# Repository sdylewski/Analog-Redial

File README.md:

**Home** · [1 · Get a board](docs/board.md) · [2 · Parts & assembly](docs/bom.md) · [3 · Flash & test](docs/flashing.md) · [4 · Set up & use](docs/setup.md)

<h1 align="center">Analog Redial</h1>

<p align="center">
  <b>Bring old telephones back to life.</b><br>
  Plug in one or two analog phones, rotary or touch-tone, and they get real
  dial tone, ringing, an operator recording and an answering machine: a complete standalone phone system.<br>
  Hackable open source hardware and software with a working web UI for configuration.</p>

<p align="center">
  <a href="#everything-it-connects-to">Overview</a> ·
  <a href="#what-can-i-do-with-it">What it does</a> ·
  <a href="#set-it-up-from-your-browser">Web interface</a> ·
  <a href="#what-does-one-cost">Cost</a> ·
  <a href="#build-one">Build one</a> ·
  <a href="#community">Community</a>
</p>

<table>
  <tr>
    <td width="50%"></td>
    <td width="50%"></td>
  </tr>
  <tr>
    <td align="center">The board: an ESP32-C6, an audio codec, with dual phone lines and the bluetooth module.</td>
    <td align="center">In its 3D-printed case <br>(<a href="https://github.com/sdylewski/Analog-Redial/blob/main/docs/case.md">case guide and print files</a>)</td>
  </tr>
</table>

## What can I do with it?

| | What you get | What you need |
|---|---|---|
| **Offline Calling** | Two phones, one board. Dial **321** (configurable) and the other phone rings.  No Wi-Fi required. Use in 2 rooms of a house or a fun toy for kids| 2 phones |
| **A phone that does things** | Dial a code and something happens: play a clip, leave a message, hear a joke. For museum exhibits, art pieces, a wedding guestbook phone. Add your own codes and audio from the browser. | One phone |
| **Call between boards** | Put a board in each room. Each gets its own 4-digit number the first time it's on your Wi-Fi; dial another board's number and its phone rings. It's VoIP over your home network: no server needed. | Two or more boards <br> Wi-Fi |
| **VoIP server** | Register a line with Asterisk, FreePBX or any SIP server and call anything that server can reach, at home or away. If the server goes down, the boards can still call each other directly. | One phone <br> Wi-Fi <br> SIP server |
| **Home Assistant** | Every pickup, hang-up and dial code becomes an event, so a dial code can turn on a light and the phone can ring when your doorbell does. Over MQTT or a plain webhook. *Experimental.* | Wi-Fi and Home Assistant (or any MQTT broker) |
| **Switch things** | Dial a code and a pin goes high for a few seconds or continuously: a relay, a buzzer, a lamp. | One line <br> no microSD <br> a relay |
| **Bluetooth calls** | Pair your mobile and the rotary phone becomes its handset: the bell rings for incoming calls, lift to answer, dial out on the rotary dial. | The BM64 Bluetooth board |

### Why not just buy a VoIP adapter?

You can do a lot with VoIP adapters and an Asterisk server, but this system can work fully offline if desired while also adding VoIP when needed.  There's also the possibility of uSD card access, bluetooth, or 4 GPIO pins to do even more.

## System overview

Every network option runs on the board's own Wi-Fi, with nothing to add.
Bluetooth is the only one that needs an extra board.

### The finer print

- **Dialing.** Rotary pulse and touch-tone, on either line. Dial codes can be
  up to 10 digits (spaces, dashes and parentheses are ignored). Add your own
  codes and audio clips from the browser and give any built-in
  code a different number. 
  	- Play an audio file after dialing a number: **412** plays dial-up modem sounds
  	- Respond to any number: **314** reads pi aloud.
  	- A kitchen timer: dial **846**, then the number of minutes, and the phone rings when time is up.
  	- An alarm clock: dial **256**, then the time (0730), and the phone rings at that time.
  	- A weather line: dial **1212** for the forecast, read out like the old time-and-temperature numbers.
  	- Optional digit readback speaks each digit you dial (**822**
  on, **821** off)
- **Calls.** Line-to-line calls with ringback and busy tones. 
	- Optional intercom mode: lift one handset, wait, and the other phone rings with its
  own double ring. 
  	- Optional VoIP calls (G.711): directly between Analog Redial boards on the same network, with no server, or through a SIP server such as Asterisk.
- **Sound.** Dial tone, ringback and busy that match your country (North
  America, several European countries, Japan, China, or a generic
  international set). Echo cancellation and earpiece volume per line. An
  off-hook alert if a handset is left off. Experimental voice effects
  (Dalek, chipmunk, robot) mid-call.
- **Messages.** Record a message with **211** and download it from the
  browser. 
  	- Optional per-line answering machine, each line with its own greeting,
  that also answers VoIP or local calls. 
  	- Storage to internal flash or microSD card for hours of storage
  (1-line version only). 
- **Payphones.** Dial tone, ringing, dialing and calls work on a payphone like
  on any phone; the coin mechanism isn't supported yet. See
  [Payphones](docs/setup.md#10-payphones).
- **Home automation.** Every pickup, hang-up, dial code and incoming ring
  can go to Home Assistant, or any system that takes a webhook or MQTT. Home
  Assistant can ring a phone or fire a pin output back. Experimental; see
  [Home Assistant](docs/home-assistant.md).
- **Things on the pins.** A dial code can switch one of four spare pins
  (a relay, a buzzer, a lamp) for a set number of seconds, or toggle it.
- **Day to day.** Quiet hours that silence the bell overnight. Remembers
  several Wi-Fi networks. An optional web password. Firmware updates from
  the browser. A one-button rescue mode for when it can't find its network.
  Board blink codes to indicate activity and errors.
- **Open.** ESP-IDF C firmware under the MIT license, KiCad hardware files,
  and a serial console for debugging.

Full feature list and firmware architecture: [Features](docs/features.md).

---

## Set it up from your browser

The board serves its own web page at **`http://phone.local`**, reachable
from any phone or laptop on your Wi-Fi. No app, no account, no cloud. On
first boot it makes its own Wi-Fi network with a setup page that gets it
onto yours. Firmware is updating frequently, so these are just examples.

<table>
  <tr>
    <td align="center" width="33%"><br><b>Status</b><br>Lines, activity, the dial guide</td>
    <td align="center" width="33%"><br><b>Phone settings</b><br>Answering machine, tones, effects</td>
    <td align="center" width="33%"><br><b>Dial codes</b><br>Your own codes and audio</td>
  </tr>
  <tr>
    <td align="center"><br><b>VoIP</b><br>SIP server, generated Asterisk script</td>
    <td align="center"><br><b>Recordings</b><br>Play or download messages</td>
    <td align="center"><br><b>Hardware</b><br>Line count, microSD, firmware update</td>
  </tr>
</table>

Click any picture for the full page. A guided tour is in
[Set up & use](docs/setup.md).

---

## What does one cost?

US prices from October 2026, including shipping and import tariff:

| | Per board | 5 boards |
|---|---:|---:|
| Assembled PCB from JLCPCB, delivered (5-board minimum) | $17.11 | $85.53 |
| Parts you solder, from DigiKey ([parts list](docs/bom.md)) | $19 | $95 |
| DigiKey shipping, about $5 an order | $1 | $5 |
| **Total, one phone line** | **about $37** | **about $186** |
| Second phone line (optional) | +$10 | +$50 |
| Bluetooth board (optional, v5) | +$15 | +$80 |

**Five boards cost about $186 in all, about $37 each.**
JLCPCB's minimum is five, so it's about $110 up front, with four spare PCBs.
The five-board Bluetooth figure is $15 a board plus about $5 shipping. Buying
the hand-solder parts from AliExpress saves $7 per board.

You'll also want a 2 A USB-C charger (or a regulated 5-6 V, 2 A DC supply for the DC jack; never 9 V or 12 V) and one or two analog phones. 

Most of a small order is fixed PCB setup fees, so boards get cheaper when people
order together. If you'd like a board,
**[fill out the interest form](https://forms.gle/kVKHiXejV6M2ZxC17)**. It's
only to show interest, so I can email you when boards are available on Tindie;
there's no commitment. Questions? [Join the Discord](https://discord.gg/zEZkqfcxqE) and ask there.

Price breakdown: [Get a board](docs/board.md#what-it-costs).

---
<br>

## Build one

No surface-mount soldering needed: the fab places the small parts, and
everything you solder is through-hole. If you can solder a header and type a
few commands in a terminal, you can build one.

| Step | Guide | What's in it |
|---|---|---|
| **1** | [Get a board](docs/board.md) | Board versions, ordering from JLCPCB, buying on Tindie, costs |
| **2** | [Parts](docs/bom.md) and [assembly](docs/building.md) | What to buy, soldering order, checks before power-on; [v5 step by step](docs/build-v5.md) |
| **3** | [Flash & test](docs/flashing.md) | Install ESP-IDF, flash the firmware, run the hardware self-test |
| **4** | [Set up & use](docs/setup.md) | Wi-Fi, the web interface, dial codes, your own audio |

Going further: [Troubleshooting](docs/troubleshooting.md) ·
[VoIP setup](docs/voip-setup.md) ·
[Home Assistant](docs/home-assistant.md) ·
[Board reference (v4)](docs/hardware-smd4.md) ·
[Board reference (v5)](docs/hardware-smd5.md) ·
[Features & firmware architecture](docs/features.md) ·
[Firmware developer notes](https://github.com/sdylewski/Analog-Redial/blob/main/firmware/README.md)

> ⚠️ **Phone lines carry real voltage.** The board drives about 48 V DC on
> an off-hook line and about 60 V AC while ringing, with peaks near 90 V.
> Don't touch the phone jacks or the line chips while it's powered, and never
> connect it to your house or telephone-company wiring. This is a hobby
> project, not certified telecom equipment.

---

## Community

- **Discord:** [join the server](https://discord.gg/zEZkqfcxqE) for questions, build help and show-and-tell
- **Want a board?** [Interest form](https://forms.gle/kVKHiXejV6M2ZxC17): just to show interest, so I can email you when boards are available on Tindie. Questions? Ask in the Discord.
- **Bugs and questions:** [GitHub Issues](https://github.com/sdylewski/Analog-Redial/issues)
- **Built one?** Post a picture in the Discord channel! We'd love to see it.

---

## Project history

| When | Version | What it was |
|------|---------|-------------|
| Aug 2020 | **Raspberry Pi** <br> | A Raspberry Pi 4 in a project box, two SLIC modules hand-wired on breadboard to the GPIO header, and a USB sound dongle per phone line. Hand written python software and shell scripts. No web UI, but it worked!|
| Jun 2026 | **v1** | The first ESP32 board: through-hole, with a WM8731 codec and two AG1170 SLICs. The Pi's job on a $5 microcontroller. Never built because boards got lost in the mail.|
| Jul 2026 | **v2** <br> | First surface-mount board: ESP32-C6 module, ES8388 codec, AG1171 SLICs, microSD. Required rework on audio lines and usb connection but it worked. |
| Sep 2026 | **v4** <br> | 2-layer, built around a cheaper 32-pin ESP32-C6-DevKitC-1, one or two phone lines, optional microSD. |
| Oct 2026 | **v5** <br>| Working: takes a genuine or clone ESP32-C6 module, and adds the expansion header (used for the Bluetooth board). <br>**With a clone module, remove the clone's bottom-right 5V pin** (see [Get a board](docs/board.md)). |
| Oct 2026 | **v5.1** | **RECOMMENDED VERSION** v5 with the clone-module 5V pin fixed (nothing to remove) and small silkscreen and fab-file updates. |
| Nov 2026 | **v6** <br> | **Released, not built or tested yet.** Two phone lines, the microSD card, payphone support and extra I/O all working at once (an I²C I/O expander drives the second line), plus the clone-module 5V pin fix and a 3 A diode (SS34) for the DC jack. |

### Related projects

Other open-source projects that bring old phones back to life:

| | [Analog Redial](https://github.com/sdylewski/Analog-Redial) | [RotaryCell](https://github.com/fregacmols/RotaryCell) | [weeBell](https://github.com/danjulio/weeBell_hardware) | [1dcoinctrl](https://github.com/hharte/1dcoinctrl) |
|---|---|---|---|---|
| **What it is** | Standalone phone system | Cellular conversion | Bluetooth adapter | Payphone coin controller |
| **MCU** | ESP32-C6 | ESP32 (LilyGO) | ESP32 (gCore) | PIC18F |
| **SLIC** | AG1171 | AG1171 | AG1171 | — |
| **Codec** | ES8388 | Passive | ES8388 | — |
| **Custom PCB** | ✅ | ✅ | ✅ | ✅ |
| **Rotary dial** | ✅ | ✅ | ✅ | ✅ |
| **Touch-tone (DTMF)** | ✅ | ❌ | ✅ | ❌ |
| **VoIP / SIP** | ✅ | ❌ | ❌ | ❌ |
| **Bluetooth calling** | ✅ | ❌ | ✅ | ❌ |
| **Cellular (SIM)** | ❌ | ✅ | ❌ | ❌ |
| **Web UI** | ✅ | ✅ Maintenance | ❌ LCD only | ❌ |
| **Answering machine** | ✅ | ❌ | ❌ | ❌ |
| **2nd phone line** | ✅ +$10 | ❌ | ❌ | ✅ Up to 4 |
| **Offline phone-to-phone** | ✅ | ❌ | ❌ | ❌ |
| **Dial codes & actions** | ✅ | ❌ | ❌ | ❌ |
| **Home automation** | ✅ | ❌ | ❌ | ❌ |
| **Payphone coin support** | In progress | ❌ | ❌ | ✅ +/-130 V |
| **OTA firmware update** | ✅ | ✅ | ❌ | ❌ |
| **Battery powered** | USB-C power bank | ✅ | ✅ | ❌ |
| **Approx. cost** | **~$37** (+$15 BT) | **~$60** + SIM | **~$60** shield + gCore (~$80-100) | **~$50-80** est. |
| **License** | MIT | MIT | CC0 | MIT |
| **GitHub stars** | — | 196 | 18 | 75 |

**RotaryCell** puts a cellular modem (LilyGO T-SIM7670G) and an AG1171
inside a rotary phone, turning it into a standalone battery-powered cell
phone with no Wi-Fi needed. It's the most polished project in the list,
with an illustrated build guide and multiple documented builds. The
published BOM is ~$52 for the core parts (LilyGO $29, PCBs $9, AG1171
$8.50, battery $5) plus a SIM card with ongoing service.

**weeBell** by [danjulio](https://github.com/danjulio) pairs a phone to
your cellphone via Bluetooth (the phone becomes a handset). It uses the
same ES8388 codec as Analog Redial, and the gCore it runs on brings a large
display. The POTS shield is
[available assembled on Tindie](https://www.tindie.com/products/30895/)
for about $60, but it also needs a [gCore](https://www.tindie.com/products/29204)
(ESP32 board with a 480 × 320 display, roughly $80-100) and an 18650
battery, so a complete build costs well over $140. weeBell replaces
danjulio's earlier Teensy-based Blue Pot.

**1dcoinctrl** by [hharte](https://github.com/hharte) is a coin-line
controller for Western Electric 1D/2D "dumb" payphones. It generates
+/-130 VDC for coin collect/refund and interfaces with Asterisk — the
closest existing project to the Analog Redial payphone coin board.
It requires a separate ATA and Asterisk server; it does not generate
dial tone or ring voltage itself. Cost is estimated at $50-80 for a
full 4-line build (PIC MCU, DC-DC converter, 7+ relays, PCB).

## License

[MIT](LICENSE) for the firmware and documentation. Hardware design files are
provided as-is for personal and hobby use; see the note in [`LICENSE`](LICENSE).

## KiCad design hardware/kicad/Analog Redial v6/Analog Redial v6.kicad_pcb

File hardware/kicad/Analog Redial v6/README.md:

# Analog Redial v6

**Released, not built or tested yet.** The KiCad project, a schematic PDF and the
JLCPCB fab files (`jlcpcb/`: gerbers, BOM and placement) are here, but no v6 board has
been built and its firmware support is untested. **v5** (`../Analog Redial v5/`) is
the tested board and **v5.1** (`../Analog Redial v5.1/`) is v5 with the
clone-module 5V pin fixed. Board reference: `docs/hardware-smd6.md`.

What v6 adds:

- **Everything at once:** two phone lines, the microSD card, payphone
  support and extra I/O all work together. On v4 and v5 the second line and
  the microSD card share the same four ESP32 pins, so a board has one or the
  other.
- **An I²C I/O expander** (TI TCA9534A, address 0x38) drives the second
  line's SLIC, which frees those ESP32 pins for the microSD card. Its four
  spare pins (P4-P7) come out on header J10 as extra I/O: the firmware drives
  them from pin dial codes (Settings → Dial Codes → Pin outputs), whatever the
  lines and microSD card are set to.
- **Payphone support:** a 5-pin I²C accessory header (1 GND, 2 SCL, 3 SDA,
  4 +3.3 V, 5 +5 V) for add-on boards such as the payphone coin board, itself
  sent to fab but untested (its firmware is in Settings → Payphone → Coin board).
- The clone-module footprint is corrected, so there is no pin to remove.
- A 3 A diode (SS34) between the DC jack and the +5 V rail instead of v5's
  1 A SS14.
- Larger vias on the power nets, teardrops, and updated silkscreen.

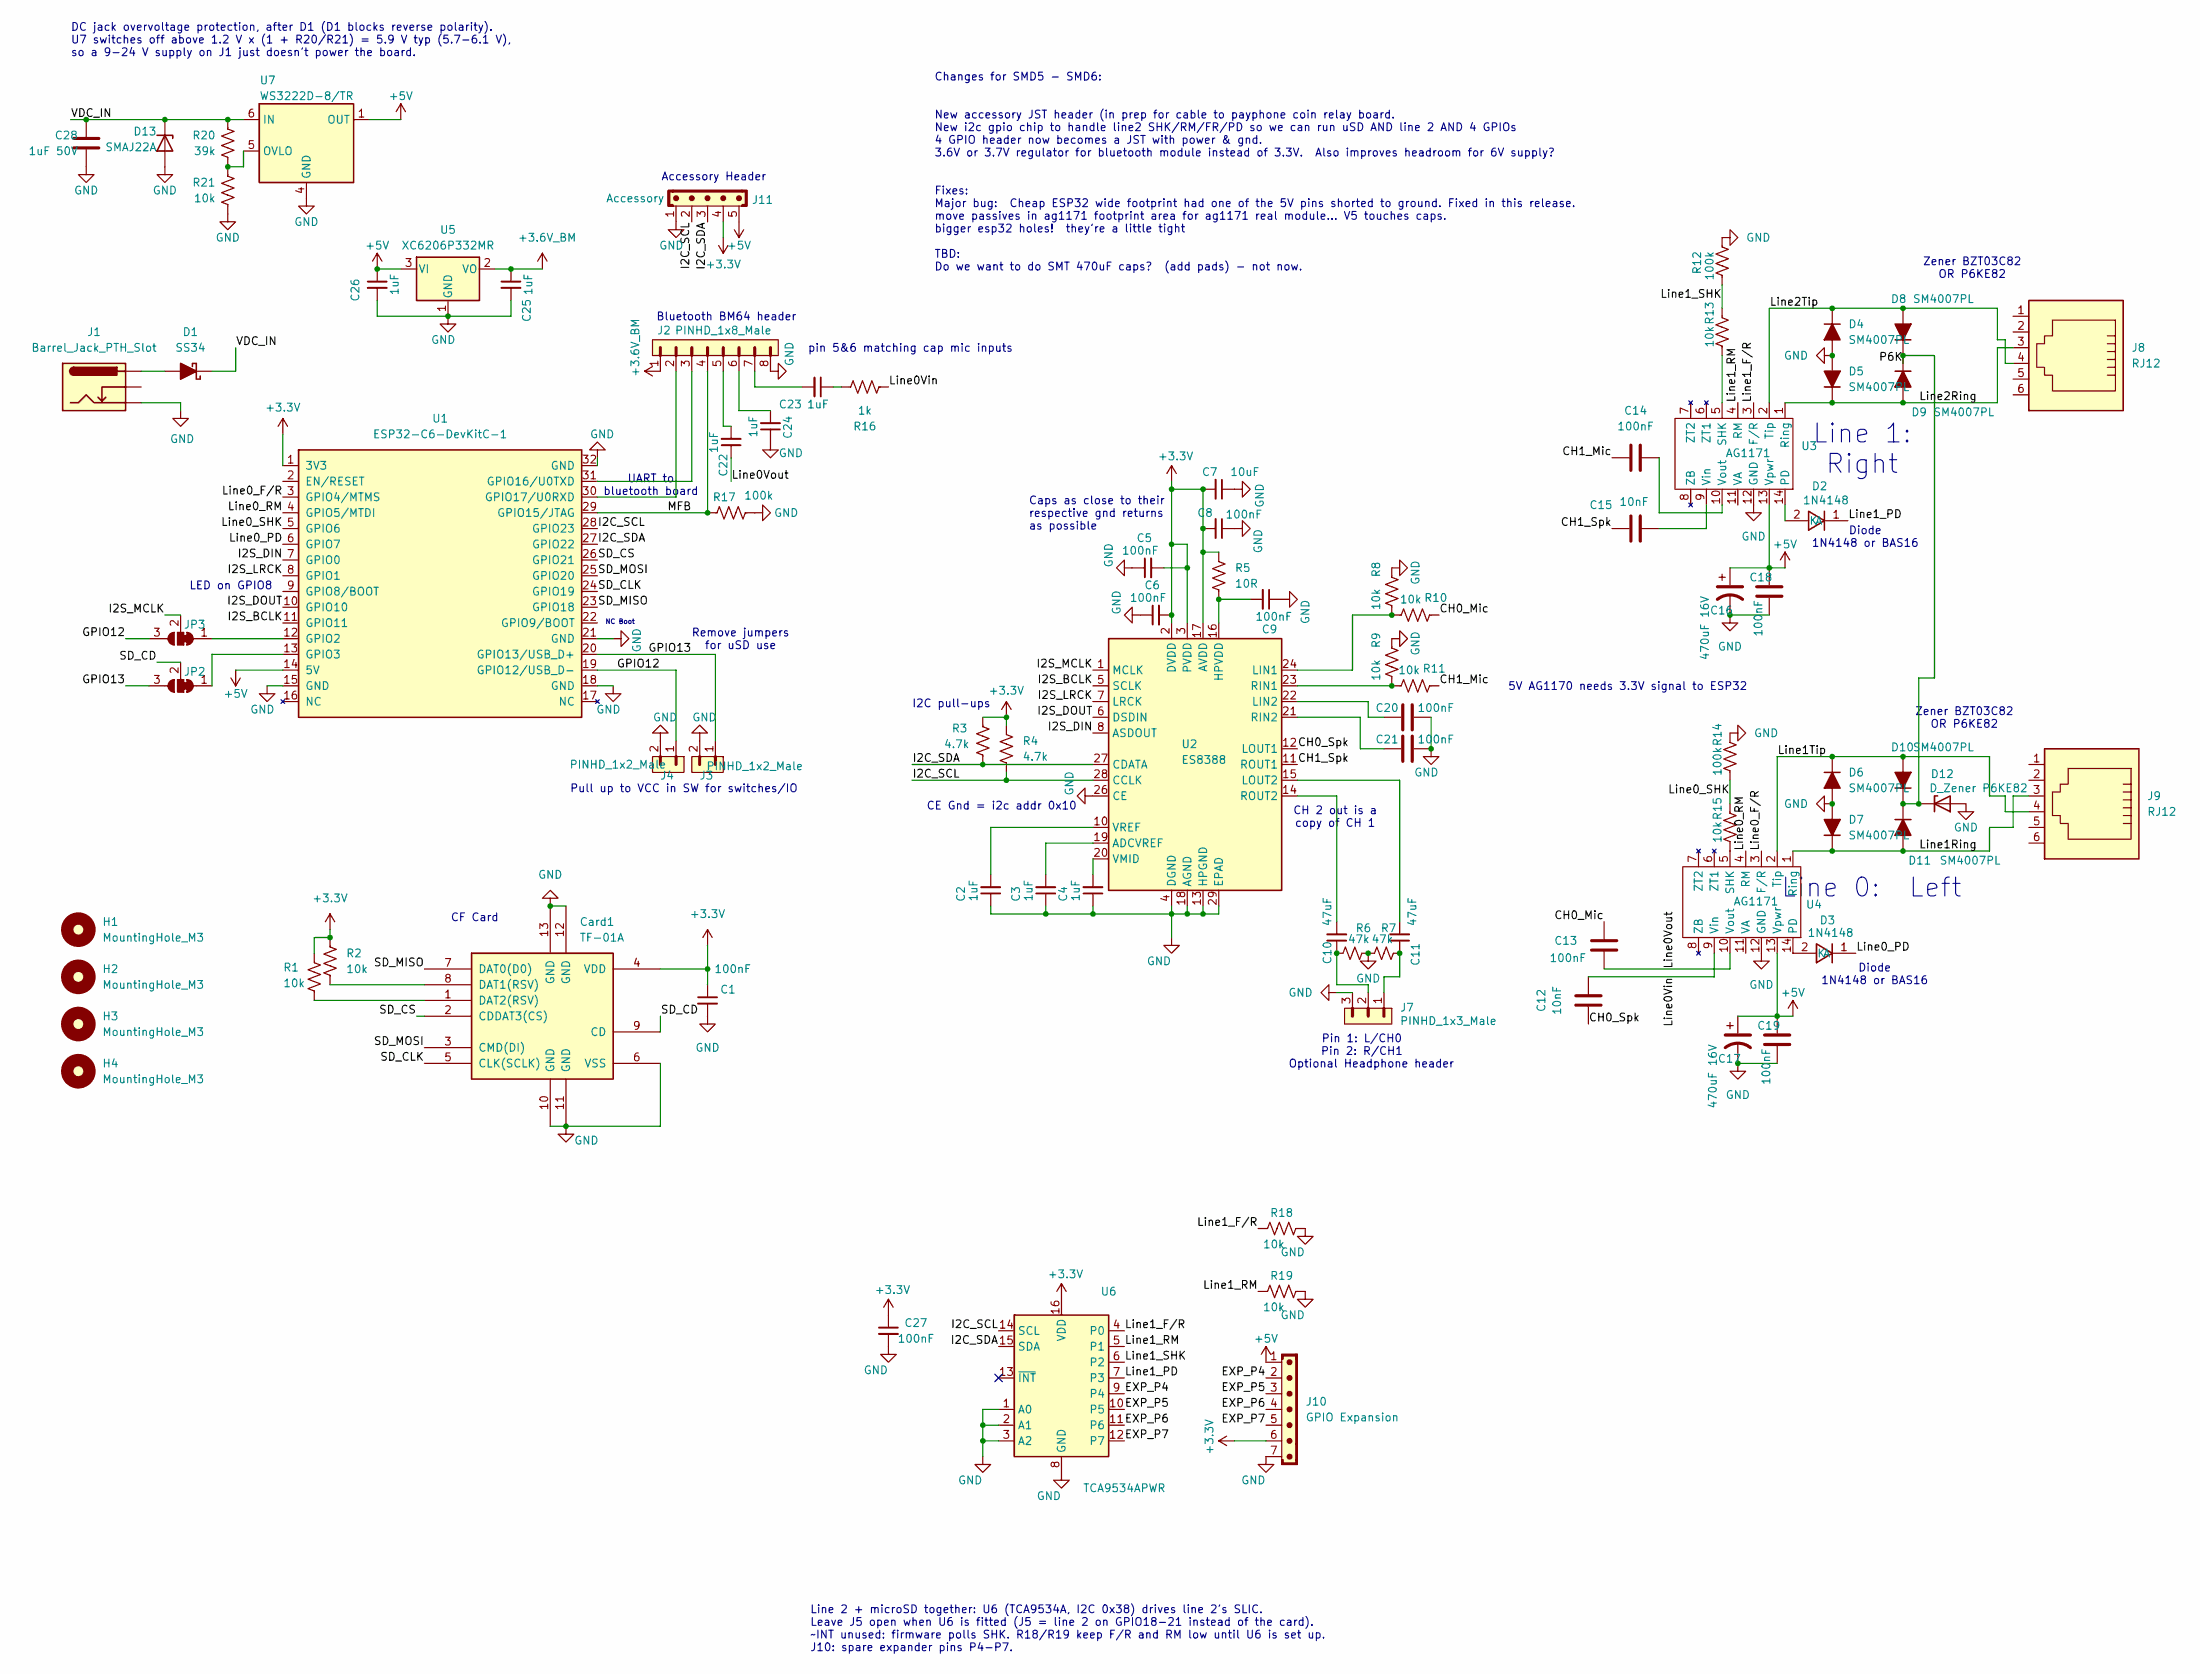
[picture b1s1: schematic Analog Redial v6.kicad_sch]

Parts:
C1, C5, C6, C8, C9, C27: 100nF; C_0402_1005Metric; Voltage 1kV; Tolerance 100%
C2, C3, C4, C22, C23, C24, C25, C26: 1uF; C_0402_1005Metric; Voltage 1kV; Tolerance 100%
C7: 10uF; C_0402_1005Metric; Voltage 1kV; Tolerance 100%
C10, C11: 47uF; C_Disc_D4.7mm_W2.5mm_P5.00mm; Voltage 1kV; Tolerance 100%
C12, C15: 10nF; C_0402_1005Metric
C13, C14, C18, C19, C20, C21: 100nF; C_0402_1005Metric
C16, C17: 470uF 16V; CP_Radial_D8.0mm_P3.50mm
C28: 1uF 50V; C_1206_3216Metric; LCSC C1848
Card1: TF-01A; Manufacturer Part TF-01A; LCSC C91145
D1: SS34; D_SMA
D2, D3: 1N4148; 1N4148W_C81598; Manufacturer Part 1N4148W; LCSC C81598
D4, D5, D6, D7, D8, D9, D10, D11: SM4007PL; Nexperia_CFP3_SOD-123W
D12: D_Zener P6KE82; D_DO-41_SOD81_P10.16mm_Horizontal
D13: SMAJ22A; D_SMA
H1, H2, H3, H4: MountingHole_M3; MountingHole_3.2mm_M3
J1: Barrel_Jack_PTH_Slot; Barrel_Jack_PTH_Slot_tight
J2: PINHD_1x8_Male; PinHeader_1x08_P2.54mm_Vertical
J3, J4: PINHD_1x2_Male; PinHeader_1x02_P2.54mm_Vertical
J7: PINHD_1x3_Male; PinHeader_1x03_P2.54mm_Vertical
J8, J9: RJ12; RJ12_Amphenol_87180_Horizontal
J10: GPIO Expansion; JST_XH_B7B-XH-A_1x07_P2.50mm_Vertical
J11: Accessory; JST_XH_B5B-XH-A_1x05_P2.50mm_Vertical
JP2, JP3: Jumper_3_NC-1_Trace_NoSilk
R1, R2, R8, R9, R10, R11, R13, R15, R18, R19: 10k; R_0402_1005Metric
R3, R4: 4.7k; R_0402_1005Metric
R5: 10R; R_0402_1005Metric
R6, R7: 47k; R_0402_1005Metric
R12, R14, R17: 100k; R_0402_1005Metric
R16: 1k; R_0402_1005Metric
R20: 39k; R_0402_1005Metric; LCSC C25783
R21: 10k; R_0402_1005Metric; LCSC C25744
U1: ESP32-C6-DevKitC-1; ESP32-C6-DevKitC-dual
U2: ES8388; QFN-28-1EP_4x4mm_P0.45mm_EP2.6x2.6mm
U3, U4: AG1171; AG1171_SIL
U5: XC6206P332MR; SOT-23-3
U6: TCA9534APWR; TSSOP-16_4.4x5mm_P0.65mm; Manufacturer Part TCA9534APWR; LCSC C206010
U7: WS3222D-8/TR; WS3222D_WDFN-8_2x2mm_P0.5mm; LCSC C239703

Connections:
+3.3V: C1.1, C5.2, C6.2, C7.2, C8.2, C27.1, Card1.4 (VDD), J10.6, J11.4, R1.2, R2.1, R3.1, R4.1, R5.1, U1.1 (3V3), U2.2 (DVDD), U2.3 (PVDD), U2.17 (AVDD), U6.16 (VDD)
+3.6V_BM: C25.1, J2.1, U5.2 (VO)
+5V: C16.1, C17.1, C18.1, C19.1, C26.1, J10.1, J11.5, U1.14 (5V), U3.13 (Vpwr), U4.13 (Vpwr), U5.3 (VI), U7.1 (OUT), U7.2 (OUT), U7.3 (OUT)
/CH0_Mic: C13.1, R10.1
/CH0_Spk: C12.1, U2.12 (LOUT1)
/CH1_Mic: C14.2, R11.1
/CH1_Spk: C15.2, U2.11 (ROUT1)
/EXP_P4: J10.2, U6.9 (P4)
/EXP_P5: J10.3, U6.10 (P5)
/EXP_P6: J10.4, U6.11 (P6)
/EXP_P7: J10.5, U6.12 (P7)
/GPIO12: J4.1, JP3.3 (B), U1.19 (GPIO12/USB_D-)
/GPIO13: J3.1, JP2.3 (B), U1.20 (GPIO13/USB_D+)
/I2C_SCL: J11.2, R4.2, U1.28 (GPIO23), U2.28 (CCLK), U6.14 (SCL)
/I2C_SDA: J11.3, R3.2, U1.27 (GPIO22), U2.27 (CDATA), U6.15 (SDA)
/I2S_BCLK: U1.11 (GPIO11), U2.5 (SCLK)
/I2S_DIN: U1.7 (GPIO0), U2.8 (ASDOUT)
/I2S_DOUT: U1.10 (GPIO10), U2.6 (DSDIN)
/I2S_LRCK: U1.8 (GPIO1), U2.7 (LRCK)
/I2S_MCLK: JP3.2 (C), U2.1 (MCLK)
/Line0Vin: C12.2, R16.1, U4.9 (Vin)
/Line0Vout: C13.2, C22.1, U4.10 (Vout)
/Line0_F/R: U1.3 (GPIO4/MTMS), U4.3 (F/R)
/Line0_PD: D3.1 (K), U1.6 (GPIO7)
/Line0_RM: U1.4 (GPIO5/MTDI), U4.4 (RM)
/Line0_SHK: R14.2, R15.1, U1.5 (GPIO6)
/Line1Ring: D7.1 (K), D11.2 (A), J9.3, U4.1 (Ring)
/Line1Tip: D6.1 (K), D10.2 (A), J9.4, U4.2 (Tip)
/Line1_F/R: R18.2, U3.3 (F/R), U6.4 (P0)
/Line1_PD: D2.1 (K), U6.7 (P3)
/Line1_RM: R19.2, U3.4 (RM), U6.5 (P1)
/Line1_SHK: R12.2, R13.1, U6.6 (P2)
/Line2Ring: D5.1 (K), D9.2 (A), J8.3, U3.1 (Ring)
/Line2Tip: D4.1 (K), D8.2 (A), J8.4, U3.2 (Tip)
/MFB: J2.4, R17.2, U1.29 (GPIO15/JTAG)
/P6K: D8.1 (K), D9.1 (K), D10.1 (K), D11.1 (K), D12.1 (K)
/SD_CD: Card1.9 (CD), JP2.2 (C)
/SD_CLK: Card1.5 (CLK(SCLK)), U1.24 (GPIO19)
/SD_CS: Card1.2 (CDDAT3(CS)), U1.26 (GPIO21)
/SD_MISO: Card1.7 (DAT0(D0)), U1.23 (GPIO18)
/SD_MOSI: Card1.3 (CMD(DI)), U1.25 (GPIO20)
/VDC_IN: C28.1, D1.1 (K), D13.1 (K), R20.1, U7.6 (IN), U7.7 (IN), U7.8 (IN)
GND: C1.2, C2.1, C3.1, C4.1, C5.1, C6.1, C7.1, C8.1, C9.1, C16.2, C17.2, C18.2, C19.2, C20.1, C21.1, C24.1, C25.2, C26.2, C27.2, C28.2, Card1.6 (VSS), Card1.10 (GND), Card1.11 (GND), Card1.12 (GND), Card1.13 (GND), D4.2 (A), D5.2 (A), D6.2 (A), D7.2 (A), D12.2 (A), D13.2 (A), J1.GND, J2.8, J3.2, J4.2, J7.3, J10.7, J11.1, R6.1, R7.2, R8.1, R9.1, R12.1, R14.1, R17.1, R18.1, R19.1, R21.2, U1.15 (GND), U1.18 (GND), U1.21 (GND), U1.32 (GND), U2.4 (DGND), U2.13 (HPGND), U2.18 (AGND), U2.26 (CE), U2.29 (EPAD), U3.12 (GND), U4.12 (GND), U5.1 (GND), U6.1 (A0), U6.2 (A1), U6.3 (A2), U6.8 (GND), U7.4 (GND), U7.9 (GND)
unnamed: C10.1, J7.2, R6.2
unnamed: C11.1, J7.1, R7.1
unnamed: C22.2, J2.5
unnamed: C23.1, R16.2
unnamed: C23.2, J2.7
unnamed: C24.2, J2.6
unnamed: Card1.8 (DAT1(RSV)), R2.2
unnamed: Card1.1 (DAT2(RSV)), R1.1
unnamed: D1.2 (A), J1.PWR
unnamed: D2.2 (A), U3.14 (PD)
unnamed: D3.2 (A), U4.14 (PD)
unnamed: JP2.1 (A), U1.13 (GPIO3)
unnamed: JP3.1 (A), U1.12 (GPIO2)
unnamed: J2.3, U1.31 (GPIO16/U0TXD)
unnamed: J2.2, U1.30 (GPIO17/U0RXD)
unnamed: C3.2, U2.19 (ADCVREF)
unnamed: C9.2, R5.2, U2.16 (HPVDD)
unnamed: R8.2, R10.2, U2.24 (LIN1)
unnamed: C20.2, U2.22 (LIN2)
unnamed: C11.2, U2.15 (LOUT2)
unnamed: R9.2, R11.2, U2.23 (RIN1)
unnamed: C21.2, U2.21 (RIN2)
unnamed: C10.2, U2.14 (ROUT2)
unnamed: C4.2, U2.20 (VMID)
unnamed: C2.2, U2.10 (VREF)
unnamed: R13.2, U3.5 (SHK)
unnamed: C15.1, U3.9 (Vin)
unnamed: C14.1, U3.10 (Vout)
unnamed: R15.2, U4.5 (SHK)
unnamed: R20.2, R21.1, U7.5 (OVLO)

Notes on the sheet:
Caps as close to their respective gnd returns as possible
pin 5&6 matching cap mic inputs
LED on GPIO8
Pin 1: L/CH0 Pin 2: R/CH1
Diode 1N4148 or BAS16
NC Boot
Line 2 + microSD together: U6 (TCA9534A, I2C 0x38) drives line 2's SLIC. Leave J5 open when U6 is fitted (J5 = line 2 on GPIO18-21 instead of the card). ~INT unused: firmware polls SHK. R18/R19 keep F/R and RM low until U6 is set up. J10: spare expander pins P4-P7.
CE Gnd = i2c addr 0x10
Remove jumpers for uSD use
CF Card
Line 1: Right
I2C pull-ups
Zener BZT03C82 OR P6KE82
UART to bluetooth board
Pull up to VCC in SW for switches/IO
CH 2 out is a copy of CH 1
Bluetooth BM64 header
Accessory Header
Line 0: Left
5V AG1170 needs 3.3V signal to ESP32
Optional Headphone header
DC jack overvoltage protection, after D1 (D1 blocks reverse polarity). U7 switches off above 1.2 V x (1 + R20/R21) = 5.9 V typ (5.7-6.1 V), so a 9-24 V supply on J1 just doesn't power the board.
Changes for SMD5 - SMD6: New accessory JST header (in prep for cable to payphone coin relay board. New i2c gpio chip to handle line2 SHK/RM/FR/PD so we can run uSD AND line 2 AND 4 GPIOs 4 GPIO header now becomes a JST with power & gnd. 3.6V or 3.7V regulator for bluetooth module instead of 3.3V. A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

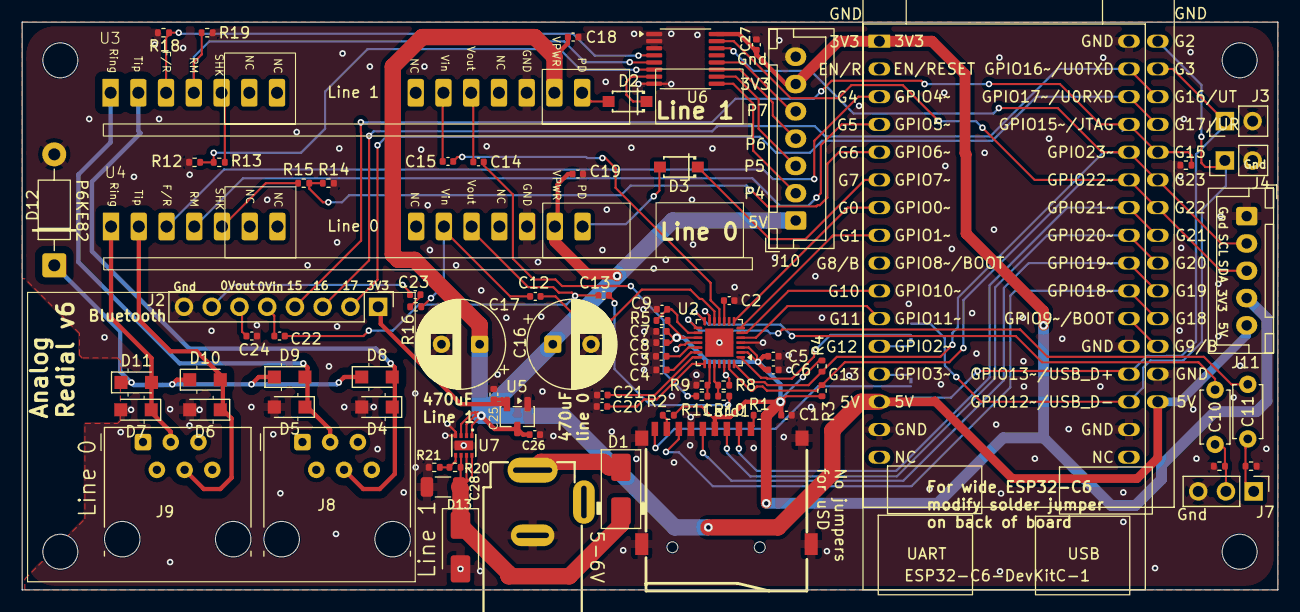
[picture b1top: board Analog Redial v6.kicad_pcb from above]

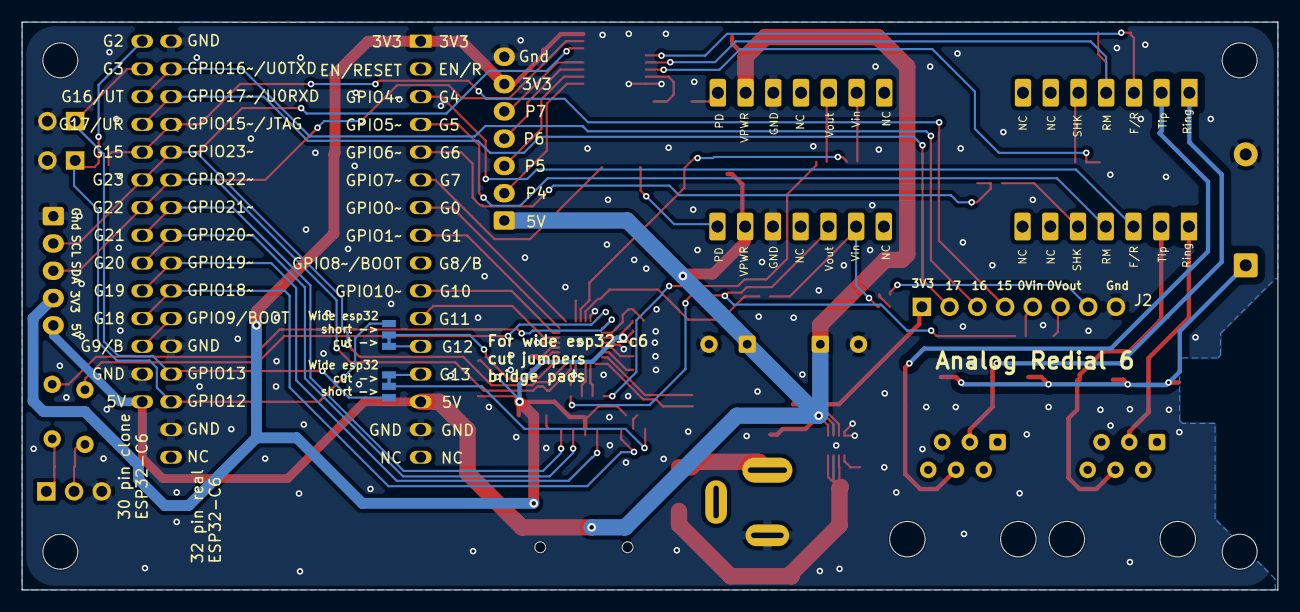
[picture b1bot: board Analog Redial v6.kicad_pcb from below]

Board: 2 copper layers, 115.0 x 52.0 mm, 85 parts (2 on the bottom side), 73 nets.

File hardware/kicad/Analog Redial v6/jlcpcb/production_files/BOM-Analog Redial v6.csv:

Comment,Designator,Footprint,LCSC,Quantity
100k,"R12,R14,R17",R_0402_1005Metric,C25741,3
100nF,"C1,C13,C14,C18,C19,C20,C21,C27,C5,C6,C8,C9",C_0402_1005Metric,C1525,12
10R,R5,R_0402_1005Metric,C25077,1
10k,"R1,R10,R11,R13,R15,R18,R19,R2,R21,R8,R9",R_0402_1005Metric,C25744,11
10nF,"C12,C15",C_0402_1005Metric,C15195,2
10uF,C7,C_0402_1005Metric,C15525,1
1N4148,"D2,D3",1N4148W_C81598,C81598,2
1k,R16,R_0402_1005Metric,C11702,1
1uF,"C2,C22,C23,C24,C25,C26,C3,C4",C_0402_1005Metric,C52923,8
1uF 50V,C28,C_1206_3216Metric,C1848,1
39k,R20,R_0402_1005Metric,C25783,1
4.7k,"R3,R4",R_0402_1005Metric,C25900,2
47k,"R6,R7",R_0402_1005Metric,C25792,2
ES8388,U2,QFN-28-1EP_4x4mm_P0.45mm_EP2.6x2.6mm,C365736,1
SM4007PL,"D10,D11,D4,D5,D6,D7,D8,D9",Nexperia_CFP3_SOD-123W,C64898,8
SMAJ22A,D13,D_SMA,C41376403,1
SS34,D1,D_SMA,C8678,1
TCA9534APWR,U6,TSSOP-16_4.4x5mm_P0.65mm,C206010,1
TF-01A,Card1,TF-01A,C91145,1
WS3222D-8/TR,U7,WS3222D_WDFN-8_2x2mm_P0.5mm,C239703,1
XC6206P332MR,U5,SOT-23-3,C5446,1
